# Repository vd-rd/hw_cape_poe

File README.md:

### Description 
This PoE modules are designed to extract power from Ethernet cables using IEEE802.3 standard, as well as providing a RMII link from the PHY onboard. Additionaly 
the board is equipped with a standard USB 2.0 dual connector. 

### Features
 * IEEE802.3 compliant (additional information can be found in [PoE Versions](docs/POE.md)
 * Input voltage range 36-57V
 * Isolated DC/DC converter
 * 10/100 Mbps PHY
 * RMII pins on header
 * USB port pins on header
 
### Resources
You can find all necesary information to build or evaluate the module here:
   - [View layout and schematic](https://cadlab.io/project/xxxx) 
   - [View 3D board render](https://a360.co/xxxx)
   - [Fabrication files](https://github.com/vd-rd/hw_cape_poe/releases)

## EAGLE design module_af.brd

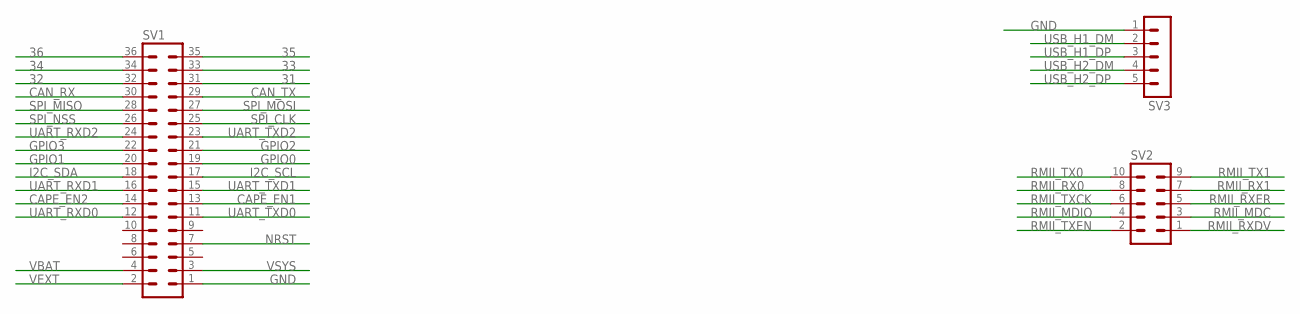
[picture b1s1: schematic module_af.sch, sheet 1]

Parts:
SV1: MA18-2
SV2: MA05-2
SV3: MA05-1

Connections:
31: SV1.31
32: SV1.32
33: SV1.33
34: SV1.34
35: SV1.35
36: SV1.36
CAN_RX: SV1.30
CAN_TX: SV1.29
CAPE_EN1: SV1.13
CAPE_EN2: SV1.14
GND: SV1.1, SV3.1; also elsewhere on the board
GPIO0: SV1.19
GPIO1: SV1.20
GPIO2: SV1.21
GPIO3: SV1.22
I2C_SCL: SV1.17
I2C_SDA: SV1.18
NRST: SV1.7
RMII_MDC: SV2.3
RMII_MDIO: SV2.4
RMII_RX0: SV2.8
RMII_RX1: SV2.7
RMII_RXDV: SV2.1
RMII_RXER: SV2.5
RMII_TX0: SV2.10
RMII_TX1: SV2.9
RMII_TXCK: SV2.6
RMII_TXEN: SV2.2
SPI_CLK: SV1.25
SPI_MISO: SV1.28
SPI_MOSI: SV1.27
SPI_NSS: SV1.26
UART_RXD0: SV1.12
UART_RXD1: SV1.16
UART_RXD2: SV1.24
UART_TXD0: SV1.11
UART_TXD1: SV1.15
UART_TXD2: SV1.23
USB_H1_DM: SV3.2
USB_H1_DP: SV3.3
USB_H2_DM: SV3.4
USB_H2_DP: SV3.5
VBAT: SV1.4
VEXT: SV1.2
VSYS: SV1.3

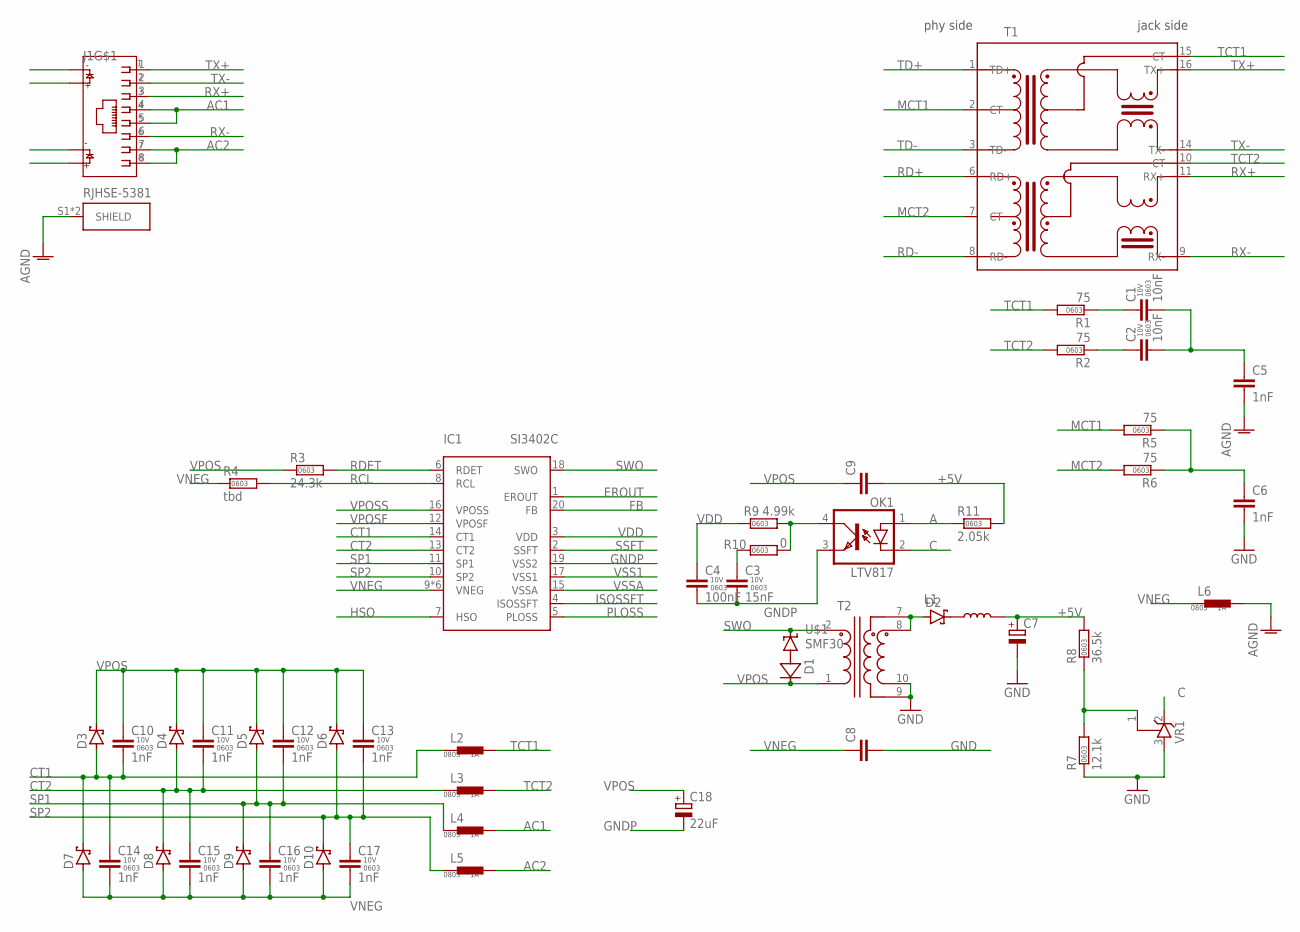
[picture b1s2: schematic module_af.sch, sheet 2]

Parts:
C1, C2: 10nF; C0603
C3: 15nF; C0603
C4: 100nF; C0603
C5, C6: 1nF; C1206
C7: CPOL-EUE5-10.5; E5-10,5
C8, C9: CAP-075-032X103; C075-032X103
C10, C11, C12, C13, C14, C15, C16, C17: 1nF; C0603
C18: 22uF; E3,5-8
D1: 1N4148WS; SOD323
D2: SCHOTTKY-DIODESMC; SMC
D3, D4, D5, D6, D7, D8, D9, D10: SK110; DO214AC
IC1: SI3402-C; QFN80P500X500X90-21T270
J1: RJHSE-5381; AMPHENOL_RJHSE-5381
L1: COIL0608-0.022; COIL0608
L2, L3, L4, L5, L6: FER-0805; FER0805
OK1: LTV817; DIL4-SMD
R1, R2, R5, R6: 75; R0603
R3: 24.3k; R0603
R4: tbd; R0603
R7: 12.1k; R0603
R8: 36.5k; R0603
R9: 4.99k; R0603
R10: 0; R0603
R11: 2.05k; R0603
T1: PT61017PEL; PT61017
T2: FA2805-CL; FA2
U$1: SMF30; SODFL3718X130
VR1: TLV431; SOT95P240X110-3

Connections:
+5V: C7.+, C9.2, L1.P$2 (2), R8.2, R11.2
A: OK1.1 (A), R11.1
AC1: J1.4, J1.5, L4.2
AC2: J1.7, J1.8, L5.2
AGND: C5.2, J1.S1 (SHIELD), J1.S2 (SHIELD), L6.2; also elsewhere on the board
C: OK1.2 (C), VR1.2 (C)
CT1: C10.2, C14.1, D3.A, D7.C, IC1.14 (CT1), L2.1
CT2: C11.2, C15.1, D4.A, D8.C, IC1.13 (CT2), L3.1
EROUT: IC1.1 (EROUT)
FB: IC1.20 (FB)
GND: C6.2, C7.-, C8.2, R7.1, T2.9, T2.10, VR1.3 (A); also elsewhere on the board
GNDP: C3.2, C4.2, C18.-, IC1.19 (VSS2), OK1.3 (EMIT)
HSO: IC1.7 (HSO)
ISOSSFT: IC1.4 (ISOSSFT)
MCT1: R5.2, T1.2 (CT)
MCT2: R6.2, T1.7 (CT)
unnamed: D2.C, L1.P$1 (1)
unnamed: C1.1, R1.1
unnamed: C1.2, C2.2, C5.1
unnamed: C6.1, R5.1, R6.1
unnamed: C2.1, R2.1
unnamed: R7.2, R8.1, VR1.1 (R)
unnamed: D2.A, T2.7, T2.8
unnamed: D1.A, U$1.A
unnamed: OK1.4 (COL), R9.2, R10.2
unnamed: C3.1, R10.1
PLOSS: IC1.5 (PLOSS)
RCL: IC1.8 (RCL), R4.2
RD+: T1.6 (RD+)
RD-: T1.8 (RD-)
RDET: IC1.6 (RDET), R3.2
RX+: J1.3, T1.11 (RX+)
RX-: J1.6, T1.9 (RX-)
SP1: C12.2, C16.1, D5.A, D9.C, IC1.11 (SP1), L4.1
SP2: C13.2, C17.1, D6.A, D10.C, IC1.10 (SP2), L5.1
SSFT: IC1.2 (SSFT)
SWO: IC1.18 (SWO), T2.2, U$1.C
TCT1: L2.2, R1.2, T1.15 (CT)
TCT2: L3.2, R2.2, T1.10 (CT)
TD+: T1.1 (TD+)
TD-: T1.3 (TD-)
TX+: J1.1, T1.16 (TX+)
TX-: J1.2, T1.14 (TX-)
VDD: C4.1, IC1.3 (VDD), R9.1
VNEG: C8.1, C14.2, C15.2, C16.2, C17.2, D7.A, D8.A, D9.A, D10.A, IC1.9 (VNEG), IC1.21 (VNEG), IC1.P$1 (VNEG), IC1.P$2 (VNEG), IC1.P$3 (VNEG), IC1.P$4 (VNEG), L6.1, R4.1
VPOS: C9.1, C10.1, C11.1, C12.1, C13.1, C18.+, D1.K (C), D3.C, D4.C, D5.C, D6.C, R3.1, T2.1
VPOSF: IC1.12 (VPOSF)
VPOSS: IC1.16 (VPOSS)
VSS1: IC1.17 (VSS1)
VSSA: IC1.15 (VSSA)

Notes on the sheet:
phy side
jack side

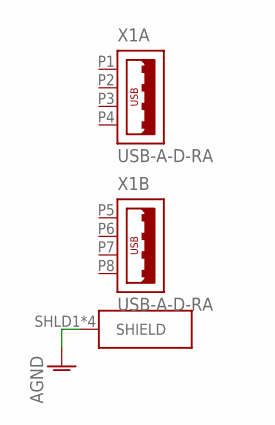
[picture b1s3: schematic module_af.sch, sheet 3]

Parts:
X1: USB-A-D-RA; DS1096

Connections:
AGND: X1.SHLD1 (SHIELD), X1.SHLD2 (SHIELD), X1.SHLD3 (SHIELD), X1.SHLD4 (SHIELD); also elsewhere on the board

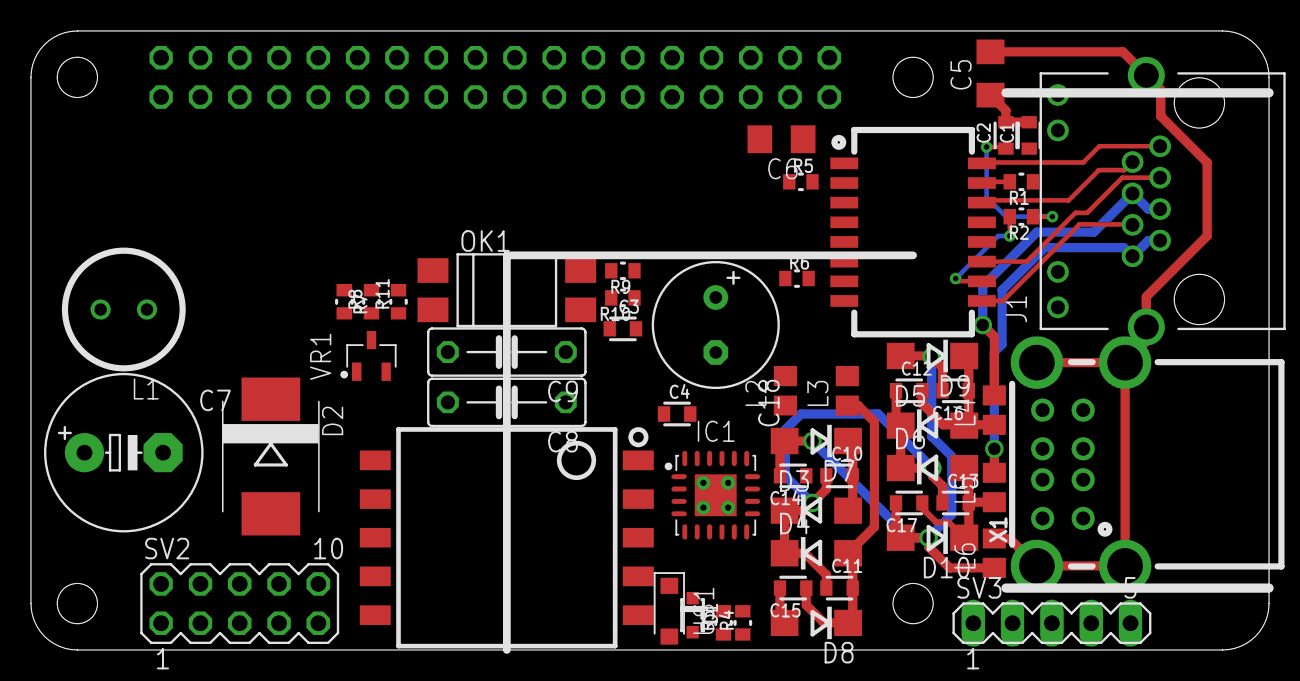
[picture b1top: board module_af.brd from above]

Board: 2 copper layers, 80.0 x 40.0 mm, 56 parts (1 on the bottom side), 36 nets.

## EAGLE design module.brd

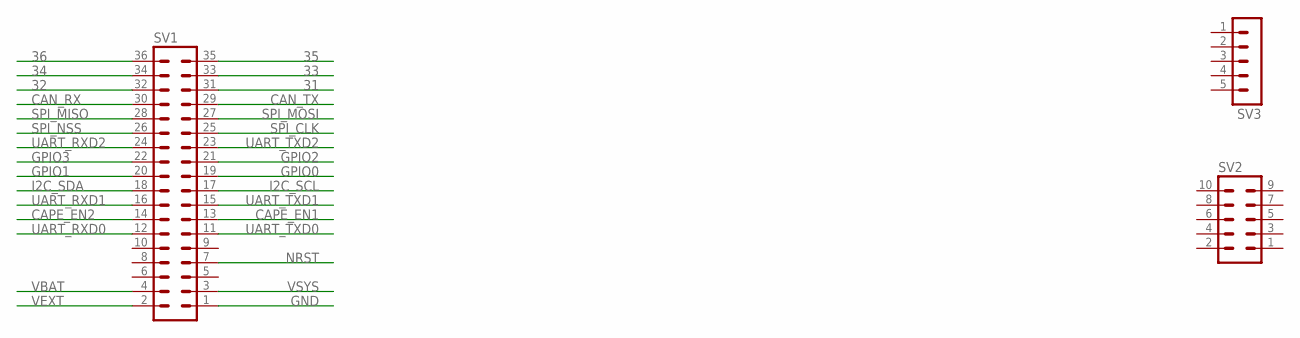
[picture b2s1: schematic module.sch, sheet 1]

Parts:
SV1: MA18-2
SV2: MA05-2
SV3: MA05-1

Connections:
31: SV1.31
32: SV1.32
33: SV1.33
34: SV1.34
35: SV1.35
36: SV1.36
CAN_RX: SV1.30
CAN_TX: SV1.29
CAPE_EN1: SV1.13
CAPE_EN2: SV1.14
GND: SV1.1; also elsewhere on the board
GPIO0: SV1.19
GPIO1: SV1.20
GPIO2: SV1.21
GPIO3: SV1.22
I2C_SCL: SV1.17
I2C_SDA: SV1.18
NRST: SV1.7
SPI_CLK: SV1.25
SPI_MISO: SV1.28
SPI_MOSI: SV1.27
SPI_NSS: SV1.26
UART_RXD0: SV1.12
UART_RXD1: SV1.16
UART_RXD2: SV1.24
UART_TXD0: SV1.11
UART_TXD1: SV1.15
UART_TXD2: SV1.23
VBAT: SV1.4
VEXT: SV1.2
VSYS: SV1.3

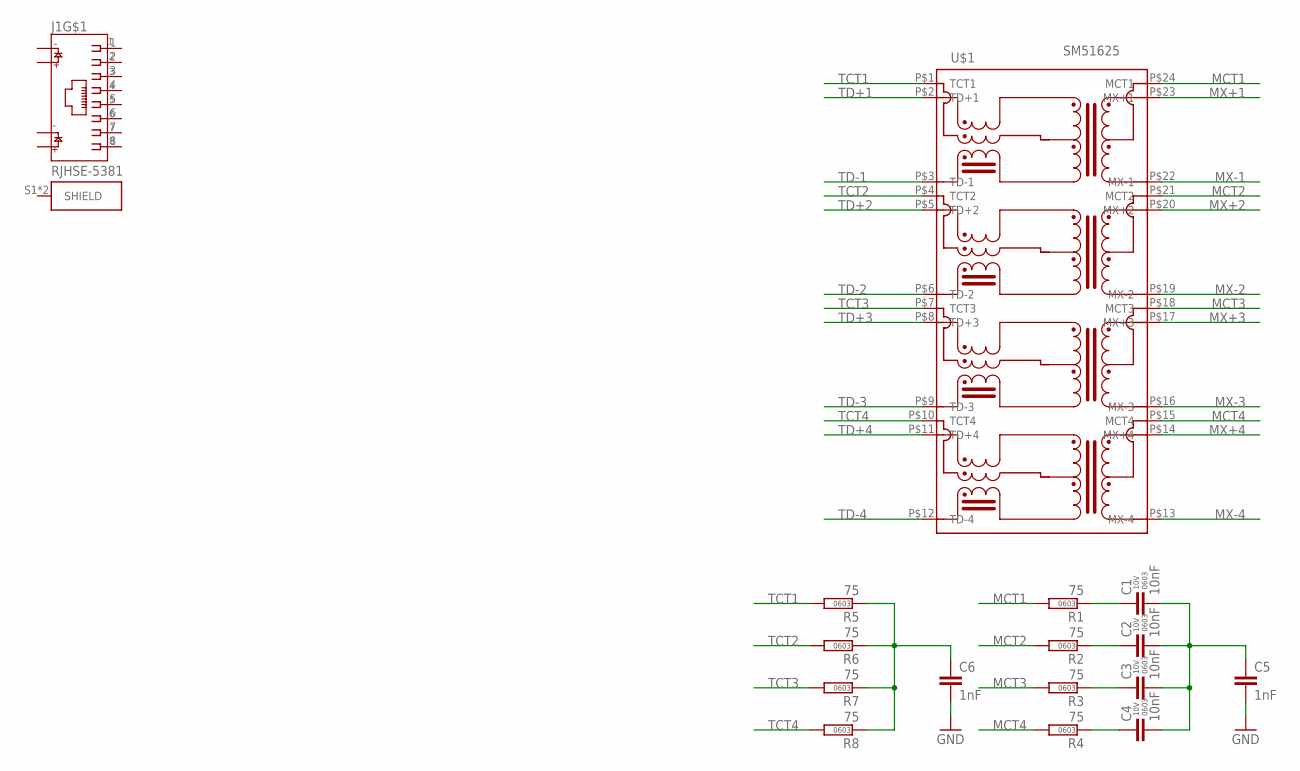
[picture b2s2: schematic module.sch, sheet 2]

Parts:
C1, C2, C3, C4: 10nF; C0603
C5, C6: 1nF; C1206
J1: RJHSE-5381; AMPHENOL_RJHSE-5381
R1, R2, R3, R4, R5, R6, R7, R8: 75; R0603
U$1: SM51625; SM61625EL

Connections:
GND: C5.2, C6.2; also elsewhere on the board
MCT1: R1.2, U$1.P$24 (MCT1)
MCT2: R2.2, U$1.P$21 (MCT2)
MCT3: R3.2, U$1.P$18 (MCT3)
MCT4: R4.2, U$1.P$15 (MCT4)
MX+1: U$1.P$23 (MX+1)
MX+2: U$1.P$20 (MX+2)
MX+3: U$1.P$17 (MX+3)
MX+4: U$1.P$14 (MX+4)
MX-1: U$1.P$22 (MX-1)
MX-2: U$1.P$19 (MX-2)
MX-3: U$1.P$16 (MX-3)
MX-4: U$1.P$13 (MX-4)
unnamed: C1.1, R1.1
unnamed: C1.2, C2.2, C3.2, C4.2, C5.1
unnamed: C6.1, R5.1, R6.1, R7.1, R8.1
unnamed: C2.1, R2.1
unnamed: C3.1, R3.1
unnamed: C4.1, R4.1
TCT1: R5.2, U$1.P$1 (TCT1)
TCT2: R6.2, U$1.P$4 (TCT2)
TCT3: R7.2, U$1.P$7 (TCT3)
TCT4: R8.2, U$1.P$10 (TCT4)
TD+1: U$1.P$2 (TD+1)
TD+2: U$1.P$5 (TD+2)
TD+3: U$1.P$8 (TD+3)
TD+4: U$1.P$11 (TD+4)
TD-1: U$1.P$3 (TD-1)
TD-2: U$1.P$6 (TD-2)
TD-3: U$1.P$9 (TD-3)
TD-4: U$1.P$12 (TD-4)

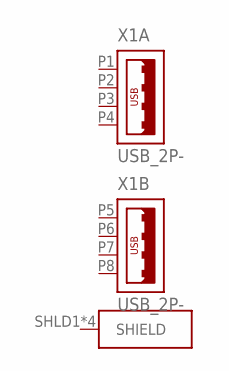
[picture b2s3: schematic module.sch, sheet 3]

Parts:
X1: USB_2P-; DS1096

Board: 2 copper layers, 20 parts (1 on the bottom side), 15 nets, no tracks yet.

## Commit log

2019-04-20 board: define shape
2019-04-20 board: defined connectors
2019-04-20 board: added magnetics
2019-04-20 board: add eth protection
2019-04-21 board: added connectors
2019-04-21 board: add 802.3af variant
2019-04-21 schematic: add isolation
2019-04-21 docs: add 802.3 presentation
2019-04-21 layout: placement updates
2019-04-22 board: improved voltage filtering
2019-04-22 board: define usb and rmii headers
2019-04-23 board: added flyback transformer
2019-04-23 board: decided solution for 15W 802.3af board
2019-04-23 board: added secondary voltage reference
2019-04-23 board: update render
2019-04-23 board: added snubber for improved switching
2019-04-23 layout: optimised component placement
2021-09-30 switch to kicad
2021-09-30 initial floorplan
2021-09-30 removed backups
2021-10-03 added isolation trafs
